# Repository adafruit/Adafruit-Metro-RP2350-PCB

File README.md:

## Adafruit Metro RP2350 PCB

<a href="http://www.adafruit.com/products/6003"><br/>
Click here to purchase one from the Adafruit shop</a>

PCB files for the Adafruit Metro RP2350. 

Format is EagleCAD schematic and board layout
* https://www.adafruit.com/product/6003

### Description

Choo! Choo! This is the RP2350 Metro Line, making all station stops at "Dual Cortex M33 mountain", "528K RAM round-about" and "16 Megabytes of Flash town". This train is piled high with hardware that complements the Raspberry Pi RP2350 chip to make it an excellent development board for projects that want Arduino-shape-compatibility or just need the extra space and debugging ports.

* RP2350 main chip, 150MHz clock, 3.3V logic
* 16 MB of QSPI flash for program storage
* 37 Available GPIO: 23 on the socket/SPI headers, 12 on HSTX port, and another 2 for USB host. 6 of which are also analog inputs
* Micro SD card socket wired up for SPI interfacing, also has extra pins connected for advanced-user SDIO interfacing (note that there's no code for SDIO in Arduino/Python, so this is a super-cutting-edge setup)
* 5V Buck Converter featuring TPS563201 6~17V DC input and up to 2A output
* Onboard RGB NeoPixel
* Onboard #23 LED
* Stemma QT port for I2C peripherals and sensors
* 22-pin 3-lane differential HSTX FPC port with 'Pi 5' compatible pinout, makes for quick DVI video output. Or, this also provides 12 extra GPIO that can be used for more pins.
* Reset and Boot buttons on PCB edge
* Pico Probe debug port - 3 pin JST SH compatible
* USB Type C power and data
* 5.5mm / 2.1mm DC jack for 6-17VDC power
* On/off switch for DC jack
* RX / TX switch for swapping D0 and D1 locations
* USB Host breakout pads - with controllable 5V power and D+/D- for bitbang USB Host.
* GPIO pin numbers match classic Arduino pins, other than GPIO 12 and 13 as those are needed for HSTX connectivity

You may be wondering about the RX-TX switch: we added this because traditional Arduino board start counting the GPIO for the digital pins with 0-7 and then 8-13. However, the D0/D1 pins are also traditionally the hardware UART Serial1, where D0 is Rx and D1 is Tx. On the RP2350, however, the UART pins are the other around: D0 is Tx and D1 is Rx. Thus a DPDT switch: flip one way to have the GPIO go in order of 0-7, flip the other way to have the logical locations of the hardware UART correct but now the pin order is 1, 0, 2, 3..7. Of course, it's also handy if, like us, you often swap the pins - now you don't need to require or cut/solder traces!

Inside the RP2350 is a 'permanent ROM' USB UF2 bootloader. What that means is when you want to program new firmware, you can hold down the BOOTSEL button while plugging it into USB (or pulling down the RUN/Reset pin to ground) and it will appear as a USB disk drive you can drag the firmware onto. Folks who have been using Adafruit products will find this very familiar - we use the technique on all our native-USB boards. Just note you don't double-click reset instead hold down BOOTSEL during boot to enter the bootloader!

There is great C/C++ support, unofficial (but really good) Arduino support, an official MicroPython port, and a CircuitPython port! We of course recommend CircuitPython because we think it's the easiest way to get started and it has support with most of our drivers, displays, sensors, and more, supported out of the box so you can follow along with our CircuitPython projects and tutorials.

While the RP2350 has lots of onboard RAM, it does not have built-in FLASH memory. Instead, that is provided by the external QSPI flash chip. On this board there is 16 MB, which is shared between the program it's running and any file storage used by MicroPython or CircuitPython. When using C/C++ you get the whole flash memory, if using Python you will have about 14 MB remaining for code, files, images, fonts, etc.

RP2350 Chip features:

* Dual ARM Cortex-M33 with floating point unit or Dual RISC-V @ 150MHz
* 520 kB on-chip SRAM
* 8 kB of one-time-programmable (OTP) memory.
* Support for up to 16MB of off-chip Flash memory via dedicated QSPI bus
* Support for external QSPI PSRAM
* DMA controller, 16 channel, 4 IRQ
* Fully-connected AHB crossbar
* On-chip switched-mode power supply and programmable low-dropout regulator (LDO) to generate core voltage
* Two on-chip PLLs to generate 48 MHz USB and 150MHz core clocks
* Optional boot signing with protected OTP storage
* Hardware SHA-256 accelerator
* Hardware random number generator (TRNG)
* 48 GPIO pins, 8 of which can be used as analog inputs
* Peripherals
	* 2 UARTs
	* 2 SPI controllers
	* 2 I2C controllers
	* 24 PWM channels (compared to 16 on RP2040)
	* USB 1.1 controller and PHY, with host and device support
	* 12 PIO state machines

Please note: The Adafruit Metro RP2350 comes with the A2 version of the RP2350, which is affected by the E9 erratum. This errata affects some uses of GPIO and PIO such as high-impedance inputs and the internal pulldowns. You may need to use 8.2K or smaller resistors if pull-downs are required. At this time, Feb 2025, there is no other version of the RP2350 available - only the A2 version.

### License

Adafruit invests time and resources providing this open source design, please support Adafruit and open-source hardware by purchasing products from [Adafruit](https://www.adafruit.com)!

Designed by Limor Fried/Ladyada for Adafruit Industries.

Creative Commons Attribution/Share-Alike, all text above must be included in any redistribution. 
See license.txt for additional details.

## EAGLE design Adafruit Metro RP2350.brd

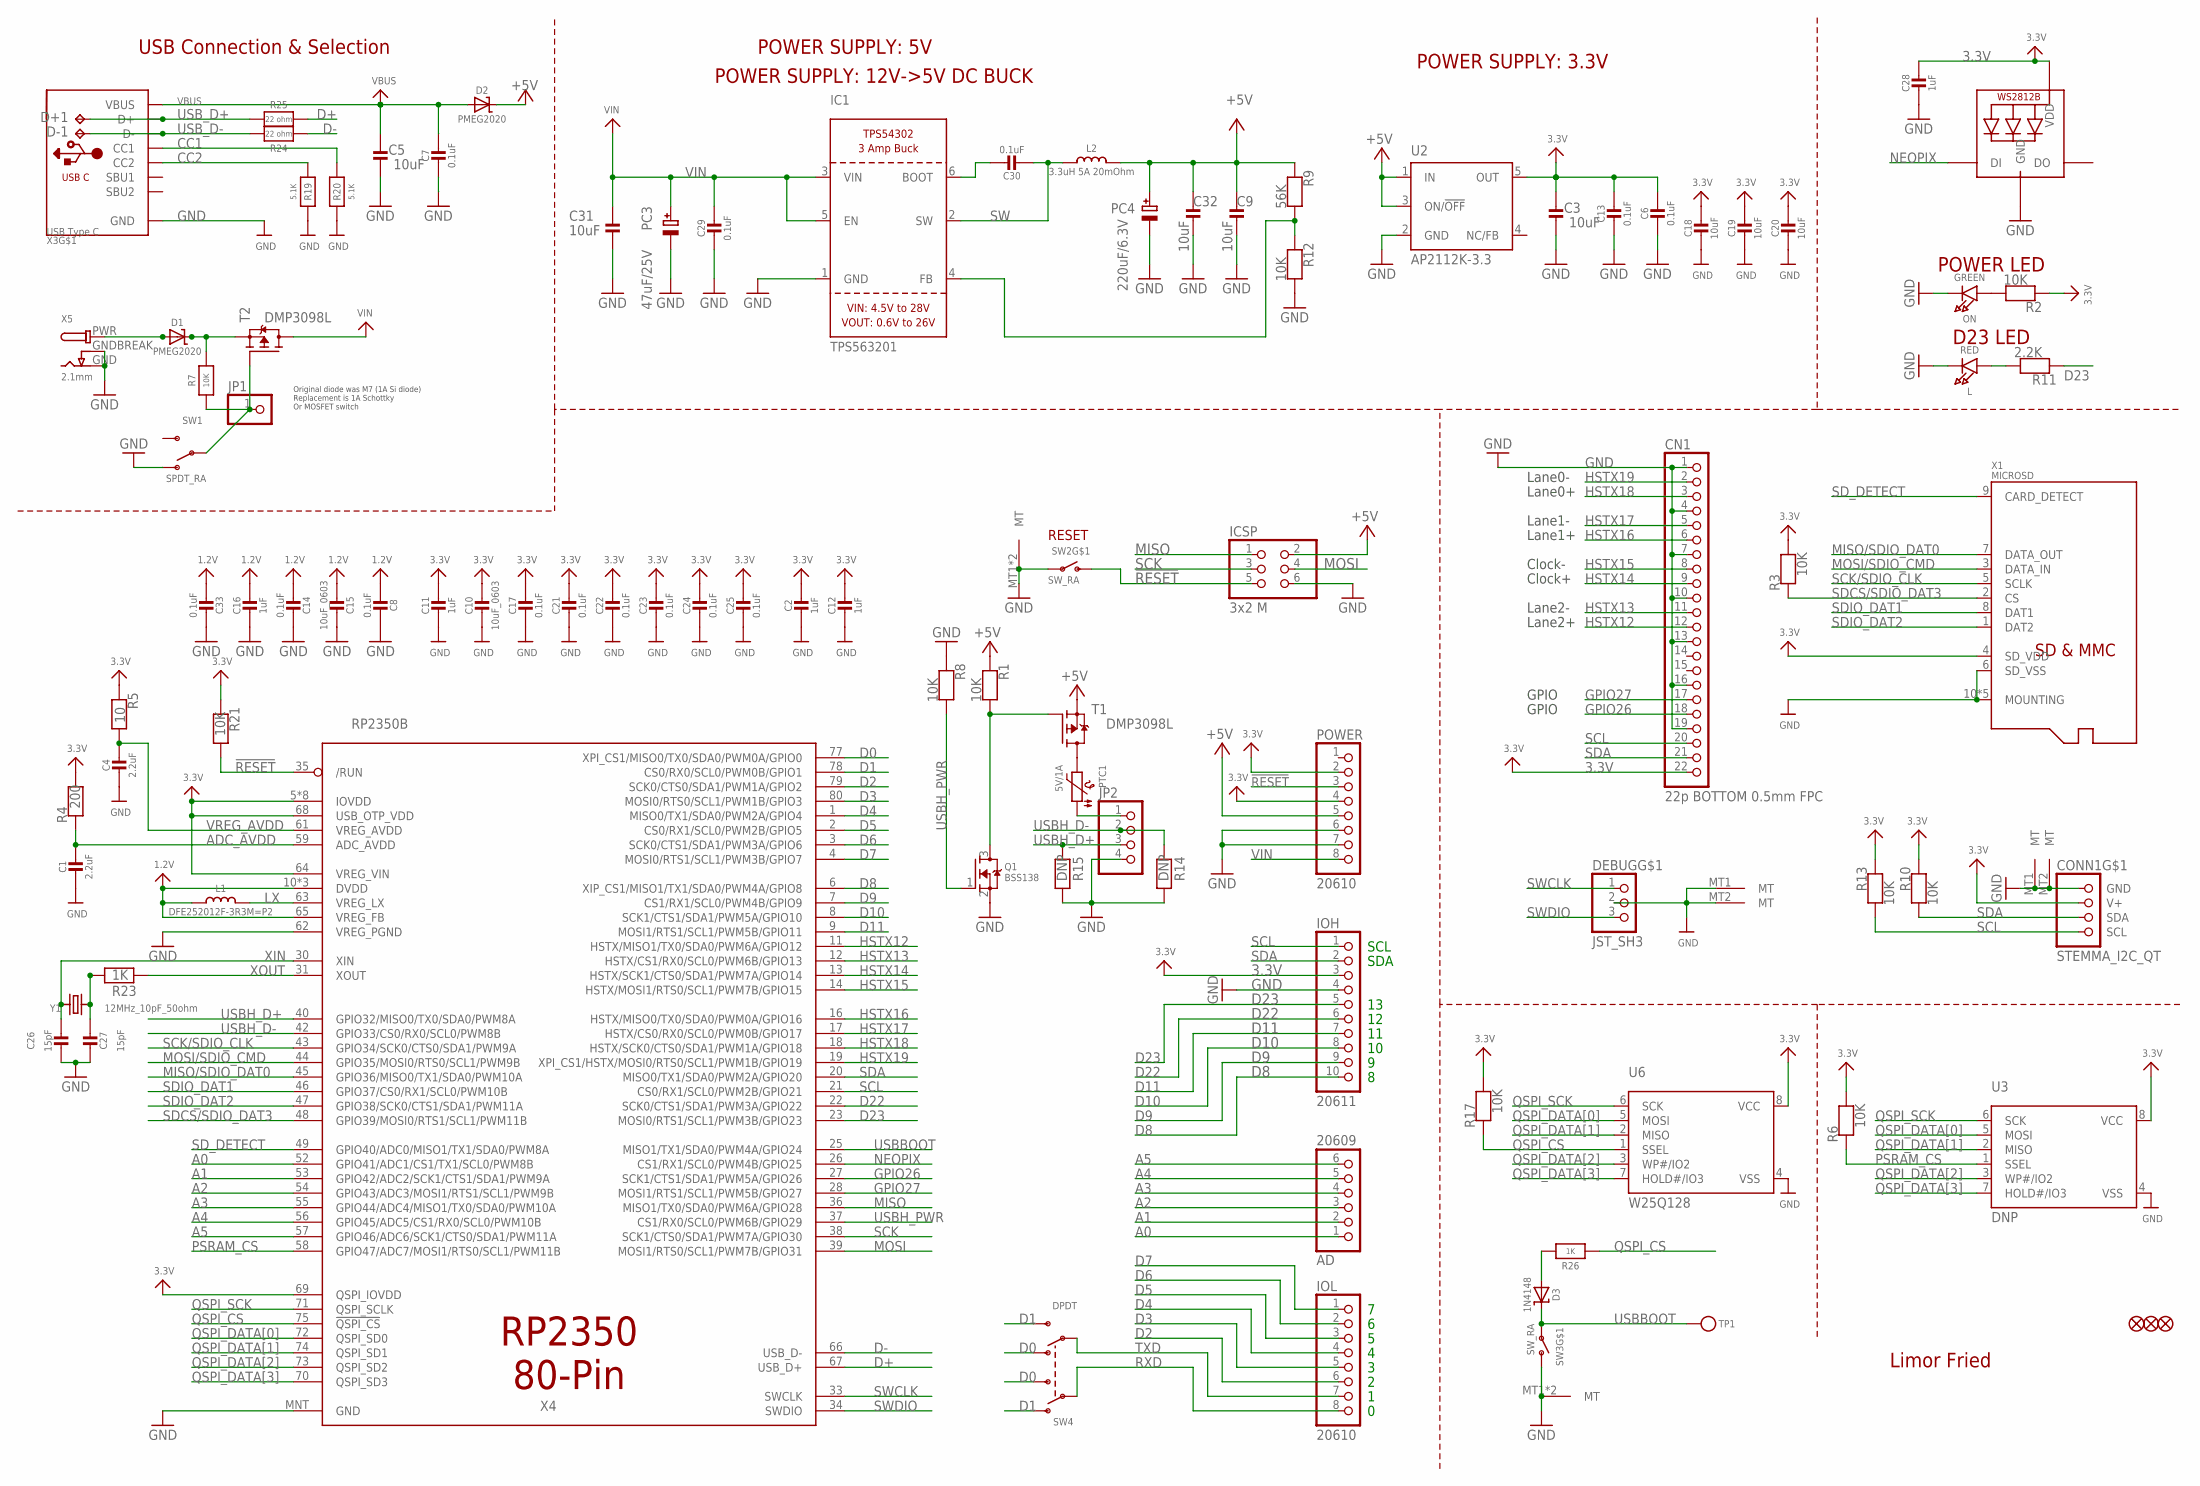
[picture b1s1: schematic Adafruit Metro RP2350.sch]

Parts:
AD: 20609; 1X06_OVALWAVE
C1, C4: 2.2uF; 0603-NO
C2, C11, C12, C16, C28: 1uF; 0603-NO
C3, C5, C9, C18, C19, C20, C31, C32: 10uF; 0805-NO
C6, C7, C8, C13, C14, C17, C21, C22, C23, C24, C25, C29, C30, C33: 0.1uF; 0603-NO
C10, C15: 10uF_0603; 0603-NO_WIDE
C26, C27: 15pF; 0603-NO
CN1: 22p BOTTOM 0.5mm FPC; FPC_22PIN
CONN1: STEMMA_I2C_QT; JST_SH4
D1, D2: PMEG2020; SOD-323
D3: 1N4148; SOD-323
D+1: TPB1,27; B1,27
D-1: TPB1,27; B1,27
DEBUG: JST_SH3; JST_SH3_RA
FD1, FD2, FD3: FIDUCIAL_1MM
IC1: TPS563201; SOT23-6
ICSP: 3x2 M; 2X03_ROUND_70MIL
IOH: 20611; 1X10_OVALWAVE
IOL: 20610; 1X08_OVALWAVE
JP1: HEADER-1X1ROUND; 1X01_ROUND
JP2: HEADER-1X4ROUND; 1X04_ROUND
L: RED; CHIPLED_0603_NOOUTLINE
L1: DFE252012F-3R3M=P2; INDUCTOR_1007
L2: 3.3uH 5A 20mOhm; INDUCTOR_0603S
LED2: WS2812B_3535FULL; LED3535_FULLPADS
ON: GREEN; CHIPLED_0603_NOOUTLINE
PC3: 47uF/25V; PANASONIC_D
PC4: 220uF/6.3V; PANASONIC_D
POWER: 20610; 1X08_OVALWAVE
PTC1: 5V/1A; 0805-NO
Q1: BSS138; SOT23-WIDE
R1, R2, R3, R6, R7, R8, R10, R12, R13, R17, R21: 10K; 0603-NO
R4: 200; 0603-NO
R5: 10; 0603-NO
R9: 56K; 0603-NO
R11: 2.2K; 0603-NO
R14, R15: DNP; 0603-NO
R19, R20: 5.1K; 0603-NO
R23, R26: 1K; 0603-NO
R24, R25: 22 ohm; 0603-NO
SW1: SPDT_RA; SPDT_SMT_SSSS811101
SW2, SW3: SW_RA; SPST_TACTILE_RA
SW4: DPDT; EG1390
T1, T2: DMP3098L; SOT23-WIDE
TP1: TESTPOINTROUND1.5MMNO; TESTPOINT_ROUND_1.5MM_NO
U2: AP2112K-3.3; SOT23-DBV
U3: DNP; SOIC8_208MIL
U6: W25Q128; SOIC8_208MIL
X1: MICROSD; MOLEX_104031-0811
X3: USB Type C; USB_C_CUSB31-CFM2AX-01-X
X4: RP2350B; QFN80
X5: 2.1mm; DCJACK_2MM_PTH
Y1: 12MHz_10pF_50ohm; CRYSTAL_2.5X2

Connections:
1.2V: C8.2, C14.2, C15.2, C16.1, C33.2, L1.P$1 (1), X4.10 (DVDD), X4.32 (DVDD), X4.51 (DVDD), X4.65 (VREG_FB)
3.3V: C2.1, C3.2, C6.2, C10.1, C11.1, C12.1, C13.1, C17.1, C18.1, C19.1, C20.1, C21.1, C22.1, C23.1, C24.1, C25.1, C28.1, CN1.22, CONN1.2 (V+), IOH.3, LED2.2 (VDD), POWER.2, POWER.4, R2.1, R3.2, R4.2, R5.1, R6.2, R10.1, R13.1, R17.2, R21.1, U2.5 (OUT), U3.8 (VCC), U6.8 (VCC), X1.4 (SD_VDD), X4.5 (IOVDD), X4.15 (IOVDD), X4.24 (IOVDD), X4.29 (IOVDD), X4.41 (IOVDD), X4.50 (IOVDD), X4.60 (IOVDD), X4.64 (VREG_VIN), X4.68 (USB_OTP_VDD), X4.69 (QSPI_IOVDD), X4.76 (IOVDD)
!RESET: ICSP.5, POWER.3, R21.2, SW2.2 (S), X4.35 (/RUN)
+5V: C9.2, C32.2, D2.C, ICSP.2, L2.P$2 (2), PC4.+, POWER.5, R1.1, R9.1, T1.2 (S), U2.1 (IN), U2.3 (ON/!OFF)
A0: AD.1, X4.52 (GPIO41/ADC1/CS1/TX1/SCL0/PWM8B)
A1: AD.2, X4.53 (GPIO42/ADC2/SCK1/CTS1/SDA1/PWM9A)
A2: AD.3, X4.54 (GPIO43/ADC3/MOSI1/RTS1/SCL1/PWM9B)
A3: AD.4, X4.55 (GPIO44/ADC4/MISO1/TX0/SDA0/PWM10A)
A4: AD.5, X4.56 (GPIO45/ADC5/CS1/RX0/SCL0/PWM10B)
A5: AD.6, X4.57 (GPIO46/ADC6/SCK1/CTS0/SDA1/PWM11A)
ADC_AVDD: C1.1, R4.1, X4.59 (ADC_AVDD)
CC1: R20.2, X3.A5 (CC1)
CC2: R19.2, X3.B5 (CC2)
D0: SW4.O2, SW4.S1, X4.77 (XPI_CS1/MISO0/TX0/SDA0/PWM0A/GPIO0)
D1: SW4.O1, SW4.S2, X4.78 (CS0/RX0/SCL0/PWM0B/GPIO1)
D2: IOL.6, X4.79 (SCK0/CTS0/SDA1/PWM1A/GPIO2)
D3: IOL.5, X4.80 (MOSI0/RTS0/SCL1/PWM1B/GPIO3)
D4: IOL.4, X4.1 (MISO0/TX1/SDA0/PWM2A/GPIO4)
D5: IOL.3, X4.2 (CS0/RX1/SCL0/PWM2B/GPIO5)
D6: IOL.2, X4.3 (SCK0/CTS1/SDA1/PWM3A/GPIO6)
D7: IOL.1, X4.4 (MOSI0/RTS1/SCL1/PWM3B/GPIO7)
D8: IOH.10, X4.6 (XIP_CS1/MISO1/TX1/SDA0/PWM4A/GPIO8)
D9: IOH.9, X4.7 (CS1/RX1/SCL0/PWM4B/GPIO9)
D10: IOH.8, X4.8 (SCK1/CTS1/SDA1/PWM5A/GPIO10)
D11: IOH.7, X4.9 (MOSI1/RTS1/SCL1/PWM5B/GPIO11)
D22: IOH.6, X4.22 (SCK0/CTS1/SDA1/PWM3A/GPIO22)
D23: IOH.5, R11.1, X4.23 (MOSI0/RTS1/SCL1/PWM3B/GPIO23)
D+: R25.2, X4.67 (USB_D+)
D-: R24.2, X4.66 (USB_D-)
GND: C1.2, C2.2, C3.1, C4.2, C5.1, C6.1, C7.2, C8.1, C9.1, C10.2, C11.2, C12.2, C13.2, C14.1, C15.1, C16.2, C17.2, C18.2, C19.2, C20.2, C21.2, C22.2, C23.2, C24.2, C25.2, C26.1, C27.1, C28.2, C29.2, C31.1, C32.1, C33.1, CN1.1, CN1.4, CN1.7, CN1.10, CN1.13, CN1.16, CN1.19, CONN1.1 (GND), CONN1.MT1 (MT), CONN1.MT2 (MT), DEBUG.2, DEBUG.MT1 (MT), DEBUG.MT2 (MT), IC1.1 (GND), ICSP.6, IOH.4, JP2.4, L.C, LED2.4 (GND), ON.C, PC3.-, PC4.-, POWER.6, POWER.7, Q1.2 (S), R8.1, R12.2, R14.1, R15.1, R19.1, R20.1, SW1.A (O), SW2.1, SW2.MT1 (MT), SW2.MT2 (MT), SW3.2 (S), SW3.MT1 (MT), SW3.MT2 (MT), U2.2 (GND), U3.4 (VSS), U6.4 (VSS), X1.6 (SD_VSS), X1.10 (MOUNTING), X1.G1 (MOUNTING), X1.G2 (MOUNTING), X1.G3 (MOUNTING), X1.G4 (MOUNTING), X3.A1B12 (GND), X3.B1A12 (GND), X4.62 (VREG_PGND), X4.MNT (GND), X5.GND, X5.GNDBREAK
GPIO26: CN1.18, X4.27 (SCK1/CTS1/SDA1/PWM5A/GPIO26)
GPIO27: CN1.17, X4.28 (MOSI1/RTS1/SCL1/PWM5B/GPIO27)
HSTX12: CN1.12, X4.11 (HSTX/MISO1/TX0/SDA0/PWM6A/GPIO12)
HSTX13: CN1.11, X4.12 (HSTX/CS1/RX0/SCL0/PWM6B/GPIO13)
HSTX14: CN1.9, X4.13 (HSTX/SCK1/CTS0/SDA1/PWM7A/GPIO14)
HSTX15: CN1.8, X4.14 (HSTX/MOSI1/RTS0/SCL1/PWM7B/GPIO15)
HSTX16: CN1.6, X4.16 (HSTX/MISO0/TX0/SDA0/PWM0A/GPIO16)
HSTX17: CN1.5, X4.17 (HSTX/CS0/RX0/SCL0/PWM0B/GPIO17)
HSTX18: CN1.3, X4.18 (HSTX/SCK0/CTS0/SDA1/PWM1A/GPIO18)
HSTX19: CN1.2, X4.19 (XPI_CS1/HSTX/MOSI0/RTS0/SCL1/PWM1B/GPIO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)
LX: L1.P$2 (2), X4.63 (VREG_LX)
MISO: ICSP.1, X4.36 (MISO1/TX0/SDA0/PWM6A/GPIO28)
MISO/SDIO_DAT0: X1.7 (DATA_OUT), X4.45 (GPIO36/MISO0/TX1/SDA0/PWM10A)
MOSI: ICSP.4, X4.39 (MOSI1/RTS0/SCL1/PWM7B/GPIO31)
MOSI/SDIO_CMD: X1.3 (DATA_IN), X4.44 (GPIO35/MOSI0/RTS0/SCL1/PWM9B)
unnamed: L.A, R11.2
unnamed: ON.A, R2.2
unnamed: JP2.1, PTC1.1
unnamed: PTC1.2, T1.3 (D)
unnamed: Q1.3 (D), R1.2, T1.1 (G)
unnamed: D3.A, R26.2
unnamed: C30.1, IC1.6 (BOOT)
unnamed: IC1.4 (FB), R9.2, R12.1
unnamed: C27.2, R23.1, Y1.3 (2)
unnamed: D1.C, R7.2, T2.2 (S)
NEOPIX: LED2.1 (DI), X4.26 (CS1/RX1/SCL0/PWM4B/GPIO25)
PSRAM_CS: R6.1, U3.1 (SSEL), X4.58 (GPIO47/ADC7/MOSI1/RTS0/SCL1/PWM11B)
PWRIN: D1.A, X5.PWR
PWR_SWITCH: JP1.1, R7.1, SW1.B, T2.1 (G)
QSPI_CS: R17.1, R26.1, U6.1 (SSEL), X4.75 (!QSPI_CS)
QSPI_DATA[0]: U3.5 (MOSI), U6.5 (MOSI), X4.72 (QSPI_SD0)
QSPI_DATA[1]: U3.2 (MISO), U6.2 (MISO), X4.74 (QSPI_SD1)
QSPI_DATA[2]: U3.3 (WP#/IO2), U6.3 (WP#/IO2), X4.73 (QSPI_SD2)
QSPI_DATA[3]: U3.7 (HOLD#/IO3), U6.7 (HOLD#/IO3), X4.70 (QSPI_SD3)
QSPI_SCK: U3.6 (SCK), U6.6 (SCK), X4.71 (QSPI_SCLK)
RXD: IOL.8, SW4.P1
SCK: ICSP.3, X4.38 (SCK1/CTS0/SDA1/PWM7A/GPIO30)
SCK/SDIO_CLK: X1.5 (SCLK), X4.43 (GPIO34/SCK0/CTS0/SDA1/PWM9A)
SCL: CN1.20, CONN1.4 (SCL), IOH.1, R13.2, X4.21 (CS0/RX1/SCL0/PWM2B/GPIO21)
SDA: CN1.21, CONN1.3 (SDA), IOH.2, R10.2, X4.20 (MISO0/TX1/SDA0/PWM2A/GPIO20)
SDCS/SDIO_DAT3: R3.1, X1.2 (CS), X4.48 (GPIO39/MOSI0/RTS1/SCL1/PWM11B)
SDIO_DAT1: X1.8 (DAT1), X4.46 (GPIO37/CS0/RX1/SCL0/PWM10B)
SDIO_DAT2: X1.1 (DAT2), X4.47 (GPIO38/SCK0/CTS1/SDA1/PWM11A)
SD_DETECT: X1.9 (CARD_DETECT), X4.49 (GPIO40/ADC0/MISO1/TX1/SDA0/PWM8A)
SW: C30.2, IC1.2 (SW), L2.P$1 (1)
SWCLK: DEBUG.1, X4.33 (SWCLK)
SWDIO: DEBUG.3, X4.34 (SWDIO)
TXD: IOL.7, SW4.P2
USBBOOT: D3.C, SW3.1, TP1.P$1, X4.25 (MISO1/TX1/SDA0/PWM4A/GPIO24)
USBH_D+: JP2.3, R15.2, X4.40 (GPIO32/MISO0/TX0/SDA0/PWM8A)
USBH_D-: JP2.2, R14.2, X4.42 (GPIO33/CS0/RX0/SCL0/PWM8B)
USBH_PWR: Q1.1 (G), R8.2, X4.37 (CS1/RX0/SCL0/PWM6B/GPIO29)
USB_D+: D+1.TP, R25.1, X3.A6 (D+), X3.B6 (D+)
USB_D-: D-1.TP, R24.1, X3.A7 (D-), X3.B7 (D-)
VBUS: C5.2, C7.1, D2.A, X3.A4B9 (VBUS), X3.B4A9 (VBUS)
VIN: C29.1, C31.2, IC1.3 (VIN), IC1.5 (EN), PC3.+, POWER.8, T2.3 (D)
VREG_AVDD: C4.1, R5.2, X4.61 (VREG_AVDD)
XIN: C26.2, X4.30 (XIN), Y1.1
XOUT: R23.2, X4.31 (XOUT)

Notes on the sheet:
SDA
SCL
Limor Fried
Original diode was M7 (1A Si diode) Replacement is 1A Schottky Or MOSFET switch
POWER SUPPLY: 5V
USB Connection & Selection
POWER SUPPLY: 3.3V
POWER LED
D23 LED
RESET
Lane0-
Lane0+
Lane1-
Lane1+
Clock-
Clock+
Lane2-
Lane2+
GPIO
POWER SUPPLY: 12V->5V DC BUCK

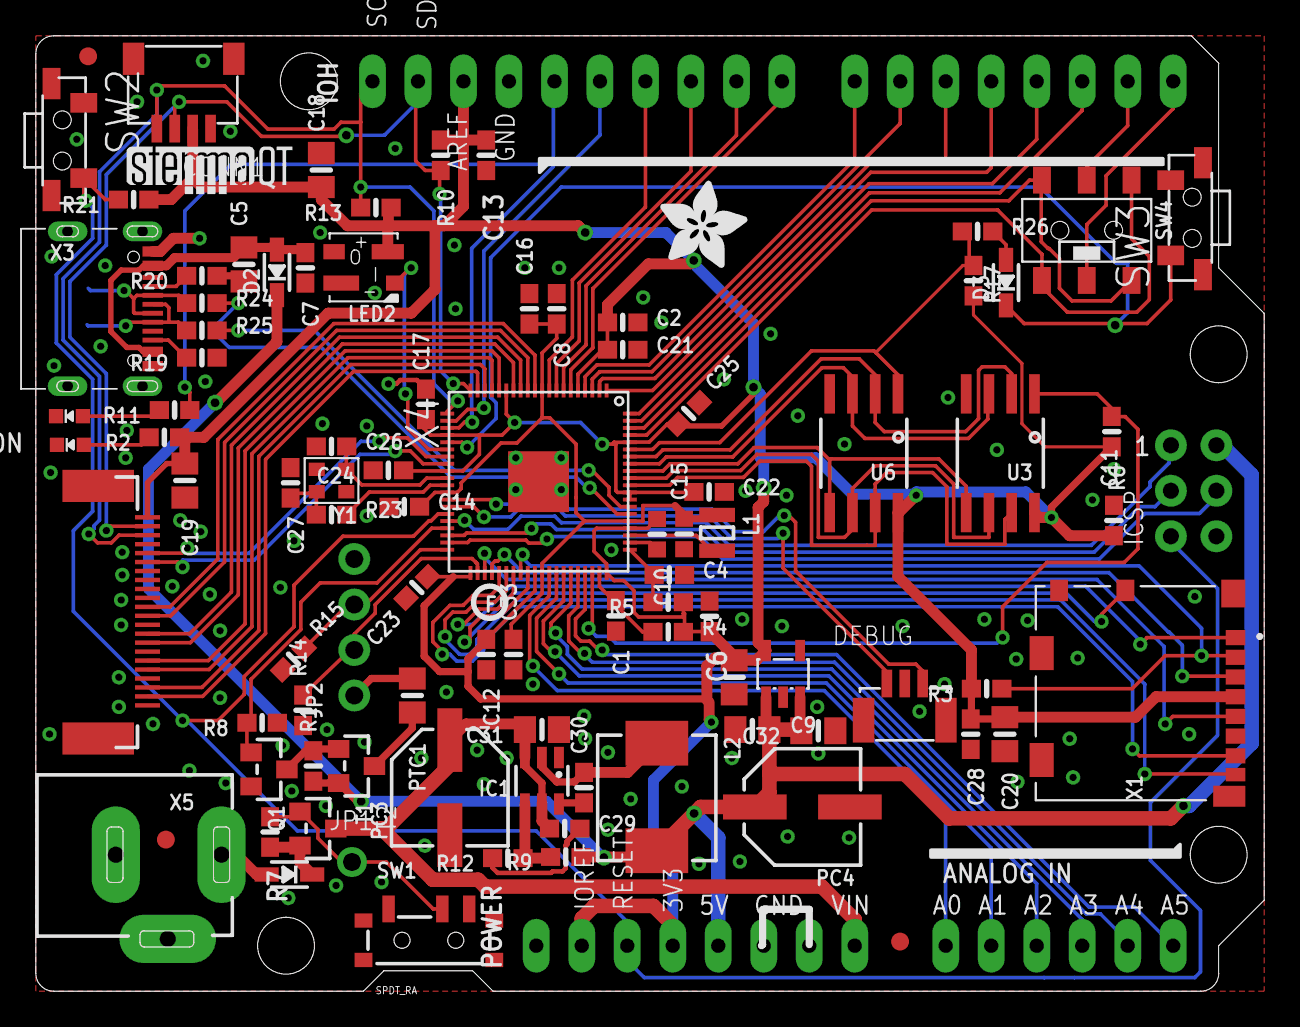
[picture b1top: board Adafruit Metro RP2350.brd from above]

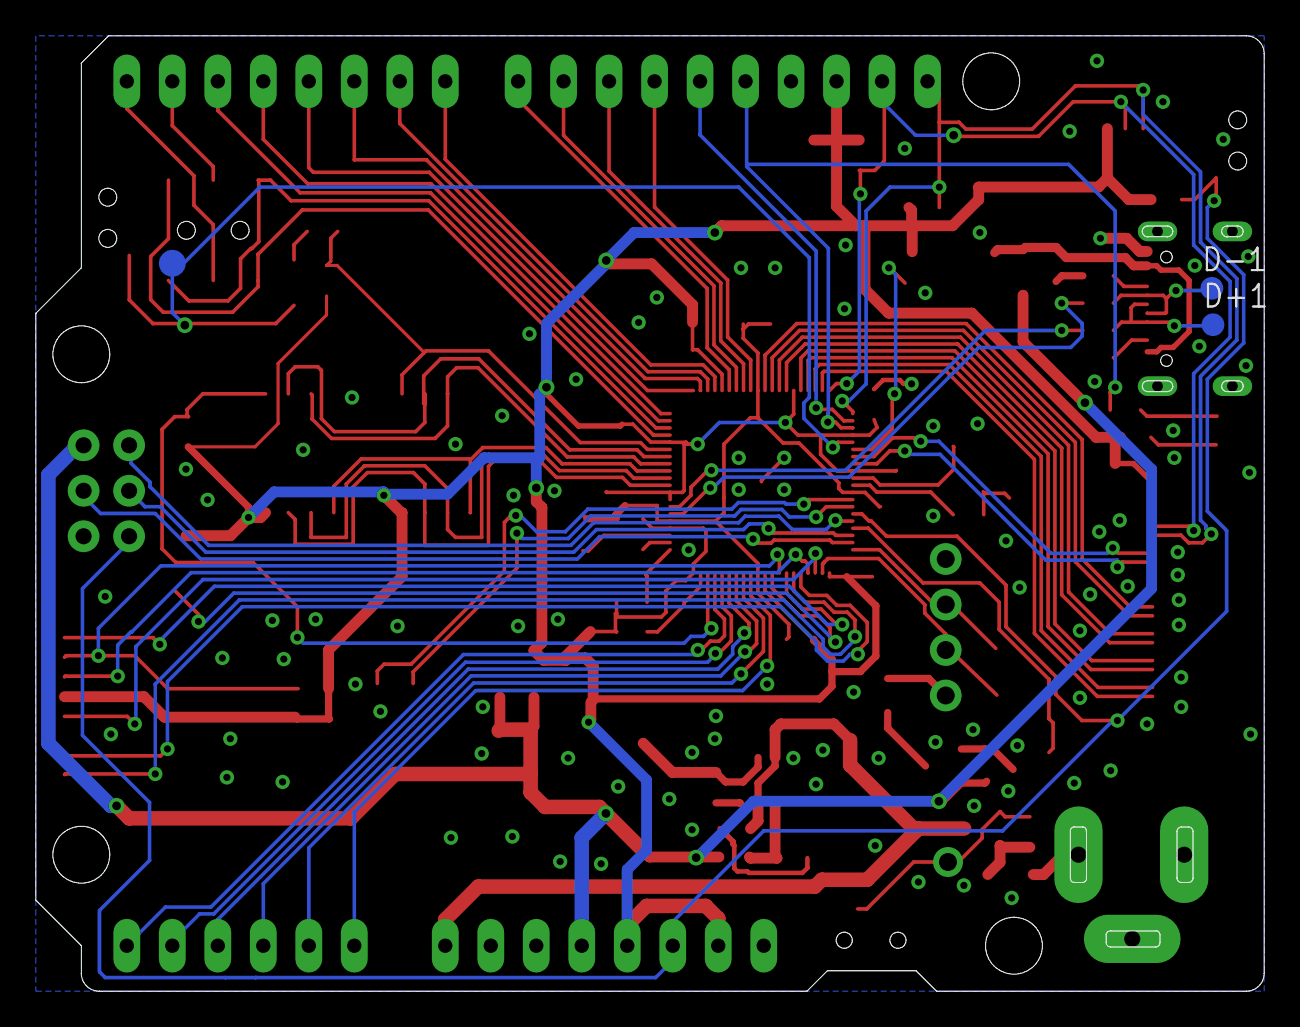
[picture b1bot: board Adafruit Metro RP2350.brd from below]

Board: 2 copper layers, 68.6 x 53.3 mm, 170 parts (5 on the bottom side), 89 nets.

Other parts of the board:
PLABEL0: PLABEL0
PLABEL1: PLABEL1
PLABEL2: PLABEL2
PLABEL3: PLABEL3
PLABEL4: PLABEL4
PLABEL5: PLABEL5
PLABEL6: PLABEL6
PLABEL7: PLABEL7
PLABEL8: PLABEL8
PLABEL10: PLABEL10
PLABEL11: PLABEL11
PLABEL12: PLABEL12
PLABEL13: PLABEL13
PLABEL14: PLABEL14
PLABEL15: PLABEL15
PLABEL16: PLABEL16
PLABEL17: PLABEL17
PLABEL18: PLABEL18
PLABEL19: PLABEL19
PLABEL20: PLABEL20
PLABEL21: PLABEL21
PLABEL22: PLABEL22
PLABEL23: PLABEL23
PLABEL24: PLABEL24
PLABEL25: PLABEL25
PLABEL26: PLABEL26
PLABEL27: PLABEL27
PLABEL28: PLABEL28
PLABEL29: PLABEL29
PLABEL30: PLABEL30
PLABEL31: PLABEL31
PLABEL32: PLABEL32
PLABEL33: PLABEL33
PLABEL34: PLABEL34
PLABEL35: PLABEL35
PLABEL36: PLABEL36
PLABEL37: PLABEL37
PLABEL38: PLABEL38
PLABEL39: PLABEL39
PLABEL40: PLABEL40
PLABEL41: PLABEL41
PLABEL42: PLABEL42
PLABEL43: PLABEL43
PLABEL46: PLABEL46
PLABEL47: PLABEL47
PLABEL48: PLABEL48
PLABEL49: PLABEL49
PLABEL50: PLABEL50
PLABEL51: PLABEL51
PLABEL52: PLABEL52
PLABEL53: PLABEL53
PLABEL54: PLABEL54
PLABEL55: PLABEL55
PLABEL56: PLABEL56
PLABEL57: PLABEL57
PLABEL59: PLABEL59
PLABEL60: PLABEL60
PLABEL62: PLABEL62
PLABEL63: PLABEL63
PLABEL64: PLABEL64
PLABEL65: PLABEL65
PLABEL66: PLABEL66
PLABEL67: PLABEL67
PLABEL68: PLABEL68
PLABEL69: PLABEL69
PLABEL70: PLABEL70
U$3: STEMMAQT
U$11: PCBFEAT-REV-040
U$47: METRO_RP2350_TOP
U$50: ADAFRUIT_5MM
U$71: METRO_RP2350_BOT

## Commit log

2024-12-18 cookiecutter
2024-12-18 eagle files
2025-01-27 final board silk
2025-02-13 prettypins

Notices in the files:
parts and their libraries:
microbuilder: This work is placed in the public domain, and may be freely used for commercial and non-commercial work with the following conditions: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
SparkFun-Aesthetics: Licensing: CC v3.0 Share-Alike You are welcome to use this library for commercial purposes.
